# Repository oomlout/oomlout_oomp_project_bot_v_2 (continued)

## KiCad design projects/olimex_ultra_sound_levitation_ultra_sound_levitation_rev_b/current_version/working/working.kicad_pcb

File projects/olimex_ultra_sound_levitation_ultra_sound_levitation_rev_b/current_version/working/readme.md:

# ultra_sound_levitation
 
## summary 
* id: olimex_ultra_sound_levitation_ultra_sound_levitation_rev_b
* user: olimex
* name: ultra_sound_levitation
* board: ultra_sound_levitation_rev_b
* repo: https://github.com/OLIMEX/Ultra-Sound-Levitation
* src_file_repo_kicad_pcb: HARDWARE/Ultra_Sound_Levitation_Rev_B/Ultra_Sound_Levitation_Rev_B.kicad_pcb
* src_file_repo_kicad_pcb_link: https://github.com/OLIMEX/Ultra-Sound-Levitation/tree/main/HARDWARE/Ultra_Sound_Levitation_Rev_B/Ultra_Sound_Levitation_Rev_B.kicad_pcb

* src_file_repo_sch: HARDWARE/Ultra_Sound_Levitation_Rev_B/Ultra_Sound_Levitation_Rev_B.sch
* src_file_repo_sch_link: https://github.com/OLIMEX/Ultra-Sound-Levitation/tree/main/HARDWARE/Ultra_Sound_Levitation_Rev_B/Ultra_Sound_Levitation_Rev_B.sch
* full details link: https://github.com/oomlout/oomlout_oomp_project_bot_v_2/tree/main/projects/olimex_ultra_sound_levitation_ultra_sound_levitation_rev_b/current_version/working

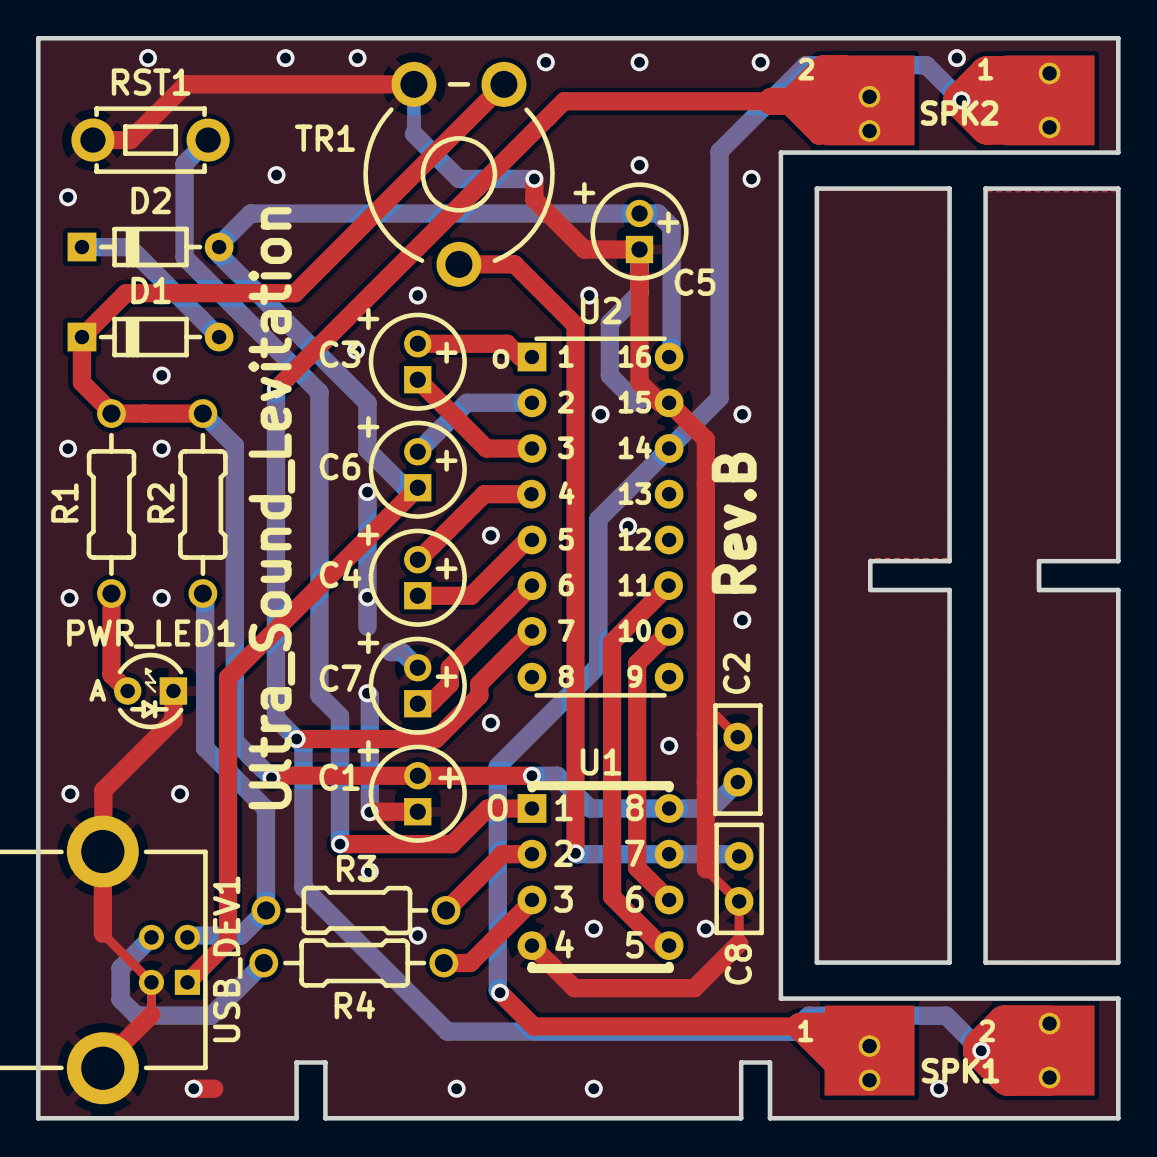
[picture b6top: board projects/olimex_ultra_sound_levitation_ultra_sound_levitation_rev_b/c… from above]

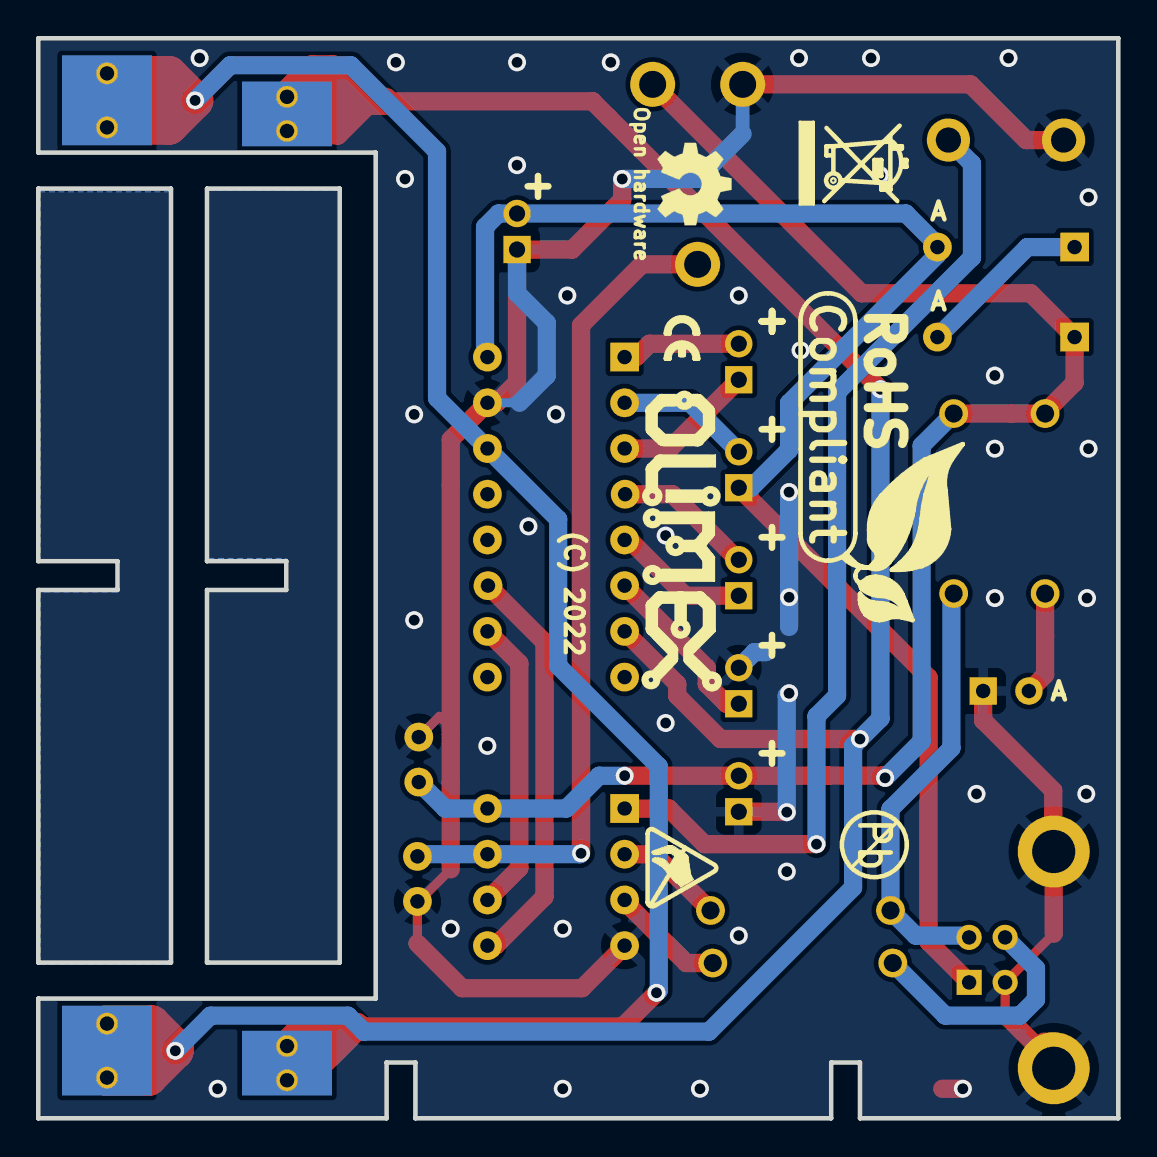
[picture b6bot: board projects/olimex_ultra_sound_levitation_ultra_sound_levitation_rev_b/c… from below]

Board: 2 copper layers, 60.0 x 60.0 mm, 29 parts (7 on the bottom side), 21 nets.

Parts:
C1, C3, C4, C5, C6, C7: 4.7uF/50V; CPOL-RM2mm_5x11mm_PTH
C2, C8: 100nF/25V/2010; C2010
D1, D2: 1N4148/DO35; DO35_1K_2A
Logo_OLIMEX_TB: Logo_OLIMEX_TB
PWR_LED1: LED/3mm/Green; LED-3mm-PTH-KA
R1, R2: 1.5k/0.25W; R_0.25W_PTH
R3, R4: 22R/0.25W; R_0.25W_PTH
RST1: T1101GP(6x3x4.3mm); T1101_GP-6x3x4.3
SPK1, SPK2: ULTRASONIC?; SPEAKER_ULTRASONIC
Sign_Antistatic_Small: Sign_Antistatic; Sign_Antistatic_4.5mmX2.8mm
Sign_CE_Small: CE_Sign_Small
Sign_OSHW_7.3x6.0mm: Sign_OSHW_7.3x6.0mm; Sign_OSHW_7.3x6.0mmn
Sign_PB-Free: Sign_PB-Free
Sign_RecycleBin_1: Sign_RecycleBin_1
Sign_RoHS_1: Sign_RoHS_1
TR1: TRIM PIHER PT10LV 10K+KNOB; TRIM_PIHER_PT10LV
U1: ATtiny85-20PU+(DIL-8); PDIP-8
U2: MAX232EN+(DIL-16); PDIP-16
USB_DEV1: USB-B(USB-SRWH-4B-LF)

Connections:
+5V: C5.1, C6.2, D2.2, U2.16, USB_DEV1.1
GND: C1.2, C2.2, C5.2, C7.1, C8.2, PWR_LED1.1, RST1.1, TR1.3, U1.4, U2.15, USB_DEV1.0, USB_DEV1.4
unnamed: C1.1, C2.1, D1.1, R1.1, R2.1, TR1.1, U1.8
unnamed: C3.1, U2.1
unnamed: C3.2, U2.3
unnamed: C4.1, U2.4
unnamed: C4.2, U2.5
unnamed: C6.1, U2.2
unnamed: C7.2, U2.6
unnamed: C8.1, TR1.2, U1.7
unnamed: D1.2, D2.1
unnamed: PWR_LED1.2, R1.2
unnamed: R2.2, R3.1, USB_DEV1.2
unnamed: R3.2, U1.2
unnamed: R4.1, USB_DEV1.3
unnamed: R4.2, U1.3
unnamed: RST1.2, U1.1
PB0_OC0A: U1.5, U2.11
PB1_OCOB: U1.6, U2.10
spout1: SPK1.1, SPK2.1, U2.14
spout2: SPK1.2, SPK2.2, U2.7

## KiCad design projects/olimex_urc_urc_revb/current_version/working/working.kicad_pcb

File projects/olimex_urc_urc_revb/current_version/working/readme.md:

# urc
 
## summary 
* id: olimex_urc_urc_revb
* user: olimex
* name: urc
* board: urc_revb
* repo: https://github.com/OLIMEX/URC
* src_file_repo_kicad_pcb: HARDWARE/URC_revB.kicad_pcb
* src_file_repo_kicad_pcb_link: https://github.com/OLIMEX/URC/tree/master/HARDWARE/URC_revB.kicad_pcb

* src_file_repo_sch: HARDWARE/URC_revB.sch
* src_file_repo_sch_link: https://github.com/OLIMEX/URC/tree/master/HARDWARE/URC_revB.sch
* full details link: https://github.com/oomlout/oomlout_oomp_project_bot_v_2/tree/main/projects/olimex_urc_urc_revb/current_version/working

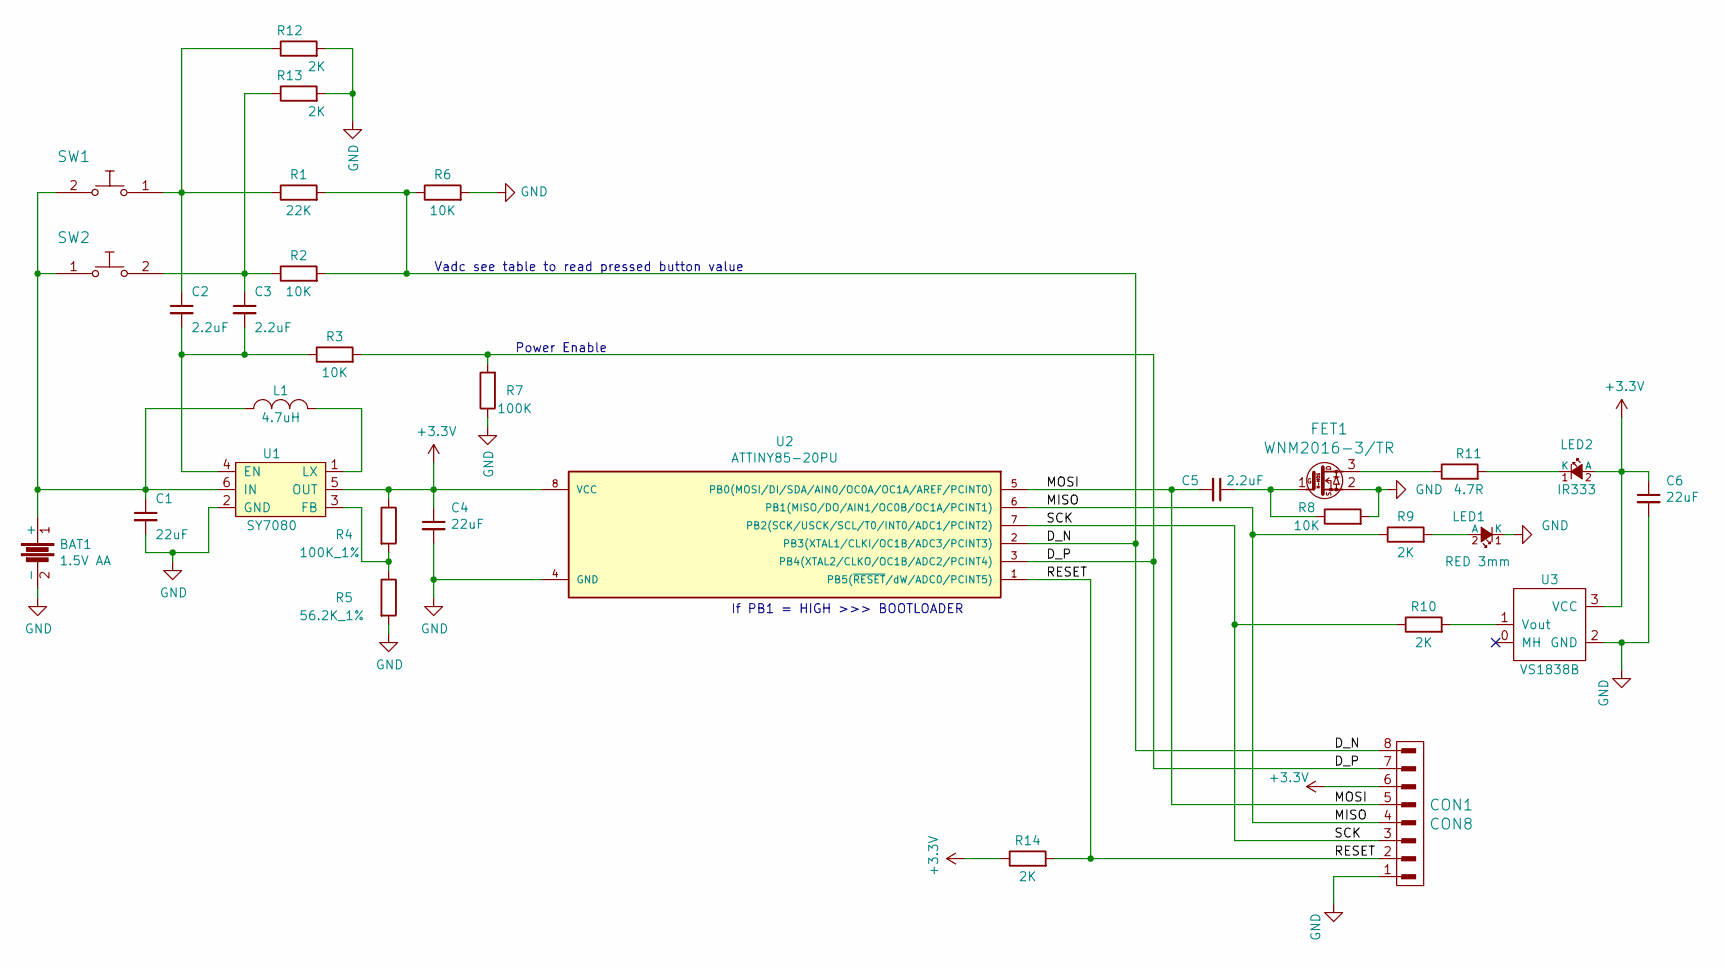
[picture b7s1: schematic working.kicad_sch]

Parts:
BAT1: 1.5V AA; BATTERY-1xAA
C1, C4, C6: 22uF; C_0805_5MIL_DWS
C2, C3, C5: 2.2uF; C_0805_5MIL_DWS
CON1: CON8; HN1x8
FET1: WNM2016-3/TR; SOT23
L1: 4.7uH; CD43
LED1: RED 3mm; LED-3mm-PTH-KA
LED2: IR333; LED3.5_2Color_side_mount
R1: 22K; R_0805_5MIL_DWS
R2, R3, R6, R8: 10K; R_0805_5MIL_DWS
R4: 100K_1%; R_0603_5MIL_DWS
R5: 56.2K_1%; R_0603_5MIL_DWS
R7: 100K; R_0805_5MIL_DWS
R9, R10, R12, R13, R14: 2K; R_0805_5MIL_DWS
R11: 4.7R; R_1206_5MIL_DWS
SW1, SW2: T1107A(6x3,8x2,5MM); T1102SMD
U1: SY7080; SOT23-6
U2: ATTINY85-20PU; SO-8_208mil
U3: VS1838B; RPM7236-H8

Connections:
+3V3: C4.1, C6.1, CON1.6, LED2.2 (A), R4.1, R14.1, U1.5 (OUT), U2.8 (VCC), U3.3 (VCC)
/D_N: CON1.8, R1.2, R2.2, R6.1, U2.2 (PB3(XTAL1/CLKI/OC1B/ADC3/PCINT3))
/D_P: CON1.7, R3.2, R7.2, U2.3 (PB4(XTAL2/CLKO/OC1B/ADC2/PCINT4))
/MISO: CON1.4, R9.1, U2.6 (PB1(MISO/DO/AIN1/OC0B/OC1A/PCINT1))
/MOSI: C5.2, CON1.5, U2.5 (PB0(MOSI/DI/SDA/AIN0/OC0A/OC1A/AREF/PCI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)
/RESET: CON1.2, R14.2, U2.1 (PB5(~RESET/dW/ADC0/PCINT5))
/SCK: CON1.3, R10.1, U2.7 (PB2(SCK/USCK/SCL/T0/INT0/ADC1/PCINT2))
GND: BAT1.2 (-), C1.2, C4.2, C6.2, CON1.1, FET1.2 (S), LED1.1 (K), R5.2, R6.2, R7.1, R8.2, R12.2, R13.2, U1.2 (GND), U2.4 (GND), U3.2 (GND)
unnamed: BAT1.1 (+), C1.1, L1.1, SW1.2, SW2.1, U1.6 (IN)
unnamed: C2.1, R1.1, R12.1, SW1.1
unnamed: C2.2, C3.2, R3.1, U1.4 (EN)
unnamed: C3.1, R2.1, R13.1, SW2.2
unnamed: C5.1, FET1.1 (G), R8.1
unnamed: FET1.3 (D), R11.1
unnamed: L1.2, U1.1 (LX)
unnamed: LED1.2 (A), R9.2
unnamed: LED2.1 (K), R11.2
unnamed: R4.2, R5.1, U1.3 (FB)
unnamed: R10.2, U3.1 (Vout)

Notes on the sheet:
If PB1 = HIGH >>> BOOTLOADER
Power Enable
Vadc see table to read pressed button value

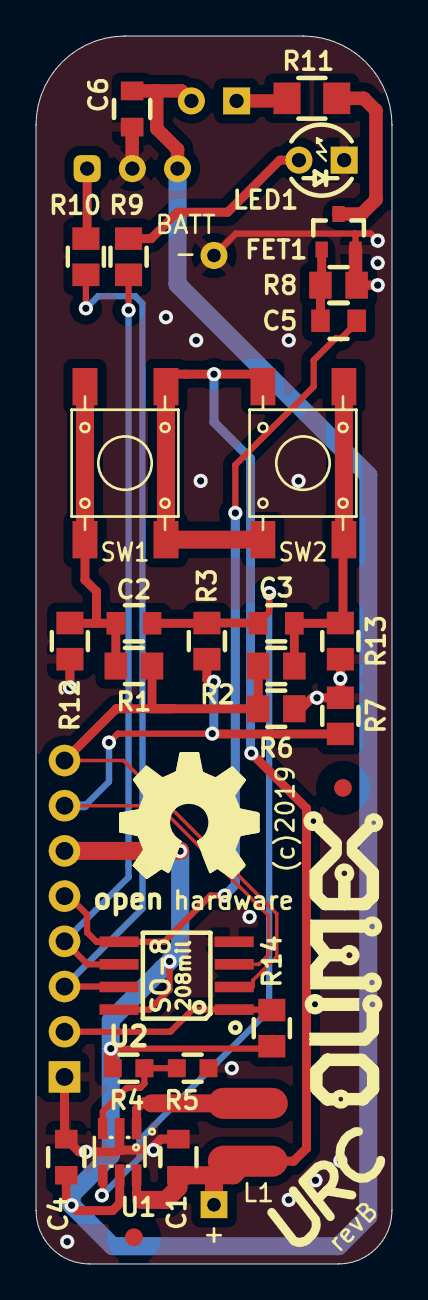
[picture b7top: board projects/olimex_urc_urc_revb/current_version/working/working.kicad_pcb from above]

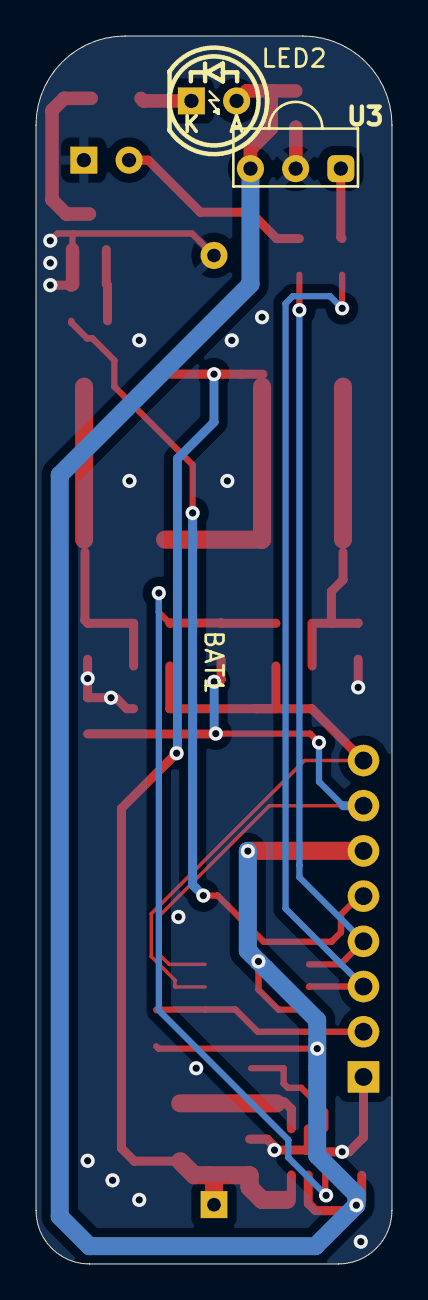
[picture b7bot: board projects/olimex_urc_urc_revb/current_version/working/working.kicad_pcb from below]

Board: 2 copper layers, 20.0 x 69.0 mm, 33 parts (3 on the bottom side), 19 nets.

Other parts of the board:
Ref*: Val**; Fiducial1x3_transp
Ref*#2: Val**; Fiducial1x3_transp
